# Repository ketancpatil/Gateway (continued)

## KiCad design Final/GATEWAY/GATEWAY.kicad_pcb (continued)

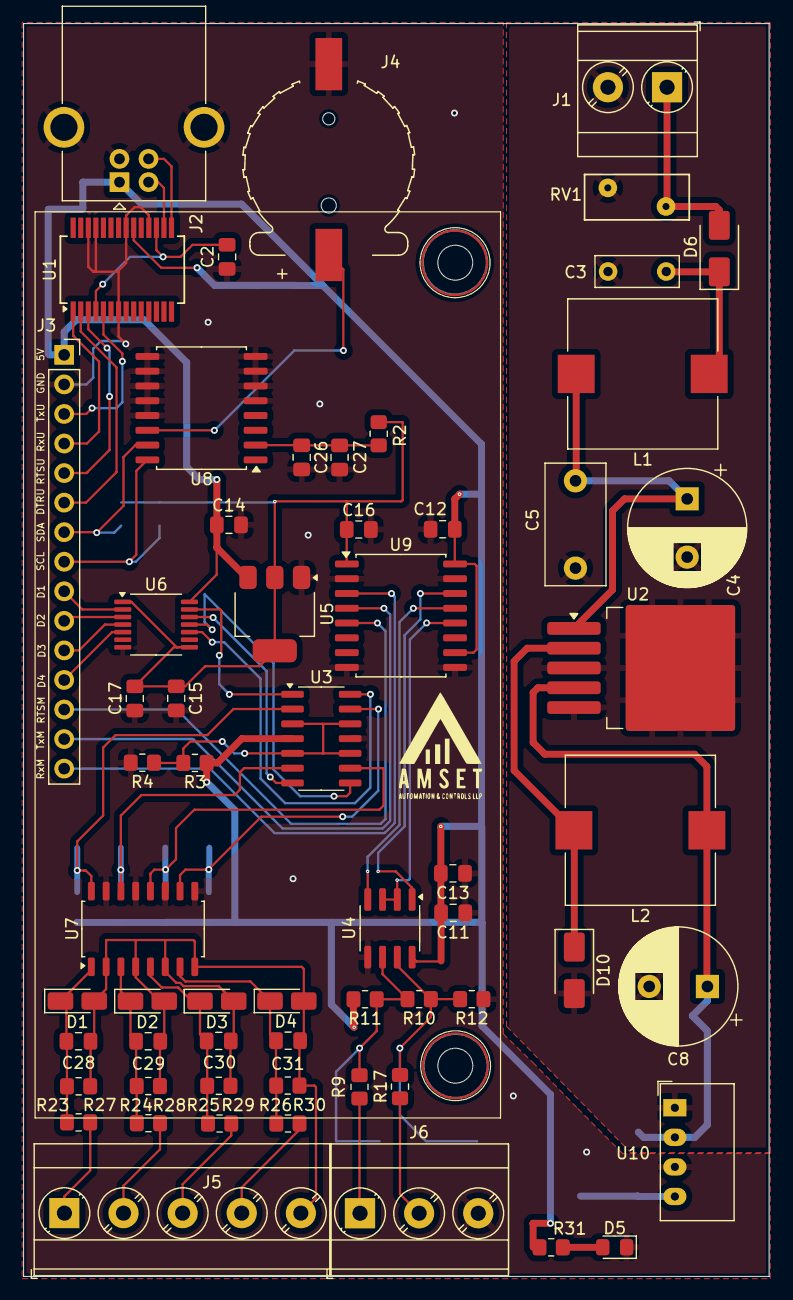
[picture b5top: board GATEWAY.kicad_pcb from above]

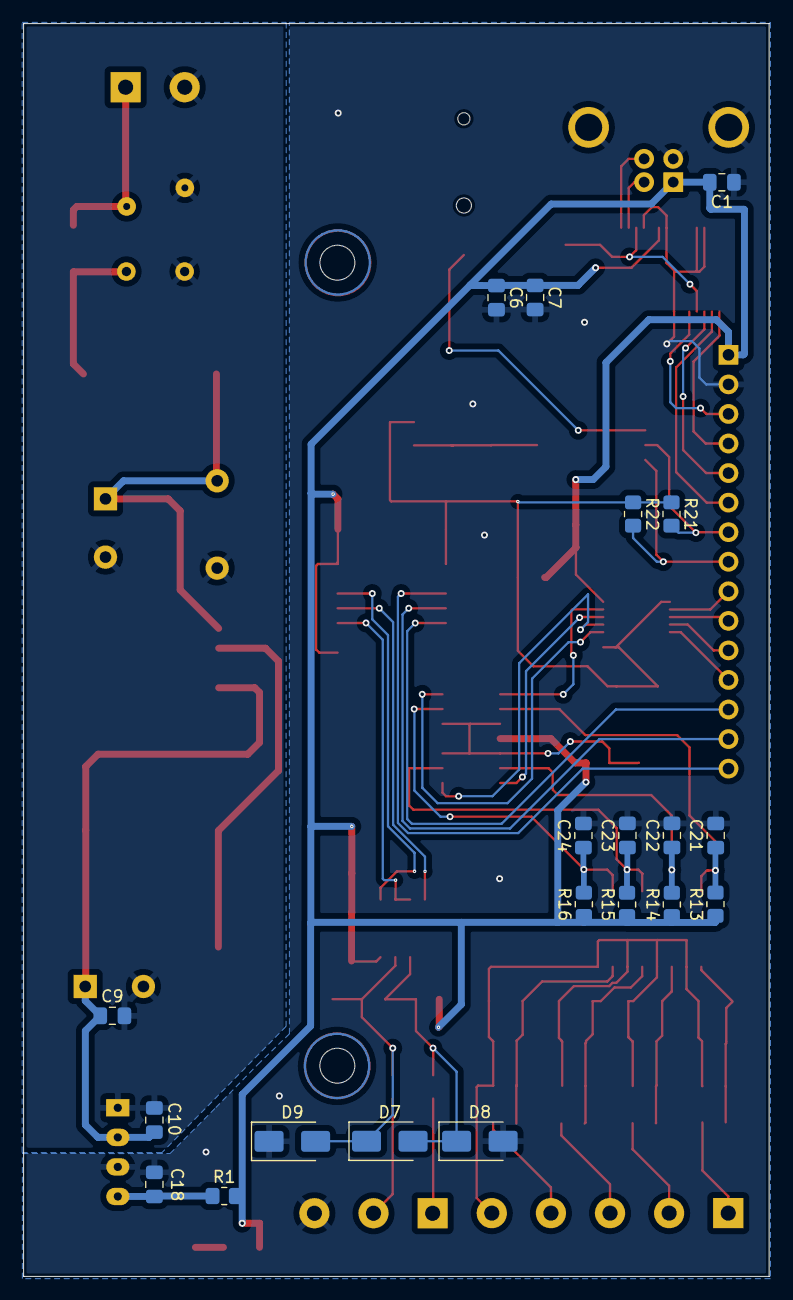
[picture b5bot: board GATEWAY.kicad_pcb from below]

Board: 2 copper layers, 64.1 x 107.7 mm, 81 parts (20 on the bottom side), 54 nets.

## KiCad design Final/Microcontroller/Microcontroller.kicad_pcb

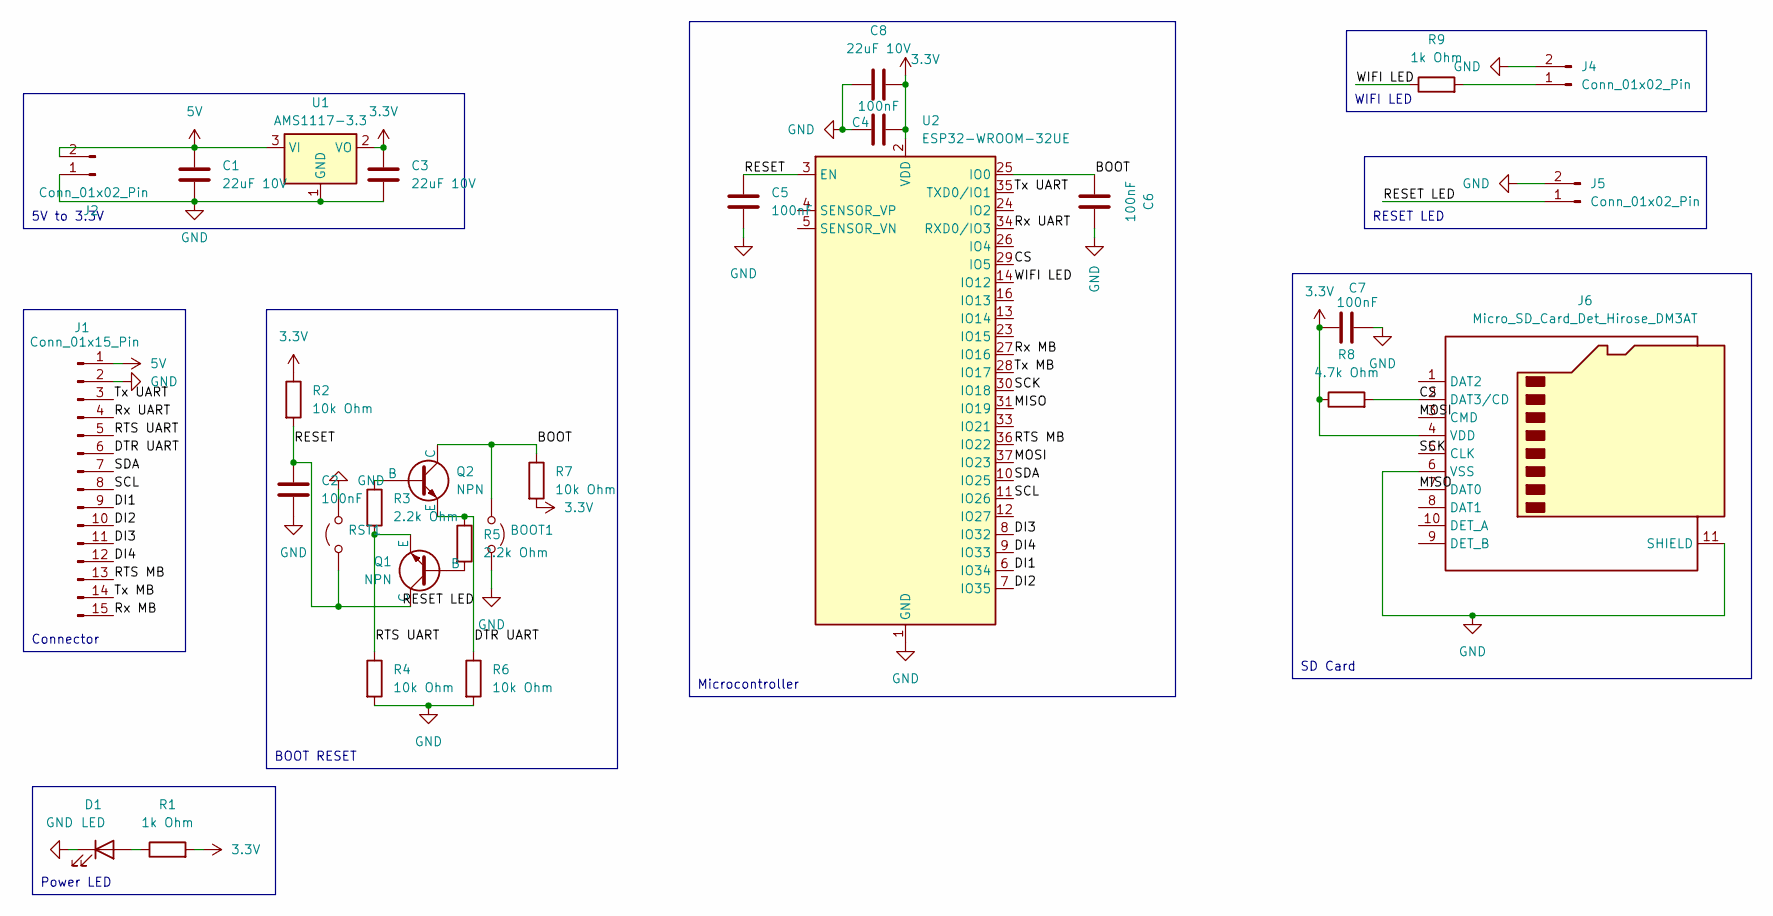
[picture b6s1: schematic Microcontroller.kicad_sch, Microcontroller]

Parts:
BOOT1: SW_SPST_CK_RS282G05A3
C1, C3, C8: 22uF 10V; C_0805_2012Metric_Pad1.18x1.45mm_HandSolder
C2, C4, C5, C6, C7: 100nF; C_0805_2012Metric_Pad1.18x1.45mm_HandSolder
D1: LED; LED_0805_2012Metric_Pad1.15x1.40mm_HandSolder
J1: Conn_01x15_Pin; PinHeader_1x15_P2.54mm_Vertical
J2, J4, J5: Conn_01x02_Pin; JST_XH_B2B-XH-A_1x02_P2.50mm_Vertical
J6: Micro_SD_Card_Det_Hirose_DM3AT; microSD_HC_Hirose_DM3AT-SF-PEJM5
Q1, Q2: NPN; SOT-23_Handsoldering
R1, R9: 1k Ohm; R_0805_2012Metric_Pad1.20x1.40mm_HandSolder
R2, R4, R6, R7: 10k Ohm; R_0805_2012Metric_Pad1.20x1.40mm_HandSolder
R3, R5: 2.2k Ohm; R_0805_2012Metric_Pad1.20x1.40mm_HandSolder
R8: 4.7k Ohm; R_0805_2012Metric_Pad1.20x1.40mm_HandSolder
RST1: JST_XH_B2B-XH-A_1x02_P2.50mm_Vertical
U1: AMS1117-3.3; SOT-223-3_TabPin2
U2: ESP32-WROOM-32UE

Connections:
3.3V: C3.1, C4.1, C7.1, C8.2, J6.4 (VDD), R1.2, R2.1, R7.2, R8.1, U1.2 (VO), U2.2 (VDD)
5V: C1.1, J1.1, J2.2, U1.3 (VI)
/BOOT: BOOT1.1 (A), C6.1, Q2.3 (C), R7.1, U2.25 (IO0)
/CS: J6.2 (DAT3/CD), R8.2, U2.29 (IO5)
/DI1: J1.9, U2.6 (IO34)
/DI2: J1.10, U2.7 (IO35)
/DI3: J1.11, U2.8 (IO32)
/DI4: J1.12, U2.9 (IO33)
/DTR UART: J1.6, Q2.2 (E), R5.1, R6.1
/MISO: J6.7 (DAT0), U2.31 (IO19)
/MOSI: J6.3 (CMD), U2.37 (IO23)
/RESET: C2.1, C5.1, J5.1, Q1.3 (C), R2.2, RST1.1 (A), U2.3 (EN)
/RTS MB: J1.13, U2.36 (IO22)
/RTS UART: J1.5, Q1.2 (E), R3.2, R4.1
/Rx MB: J1.15, U2.27 (IO16)
/Rx UART: J1.4, U2.34 (RXD0/IO3)
/SCK: J6.5 (CLK), U2.30 (IO18)
/SCL: J1.8, U2.11 (IO26)
/SDA: J1.7, U2.10 (IO25)
/Tx MB: J1.14, U2.28 (IO17)
/Tx UART: J1.3, U2.35 (TXD0/IO1)
/WIFI LED: R9.1, U2.14 (IO12)
GND: BOOT1.2 (B), C1.2, C2.2, C3.2, C4.2, C5.2, C6.2, C7.2, C8.1, D1.1 (K), J1.2, J2.1, J4.2, J5.2, J6.6 (VSS), J6.11 (SHIELD), R4.2, R6.2, RST1.2 (B), U1.1 (GND), U2.1 (GND), U2.15 (GND), U2.38 (GND), U2.39 (GND)
unnamed: D1.2 (A), R1.1
unnamed: J4.1, R9.2
unnamed: Q1.1 (B), R5.2
unnamed: Q2.1 (B), R3.1

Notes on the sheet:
Power LED
5V to 3.3V
WIFI LED
SD Card
Microcontroller
Connector
RESET LED
BOOT RESET

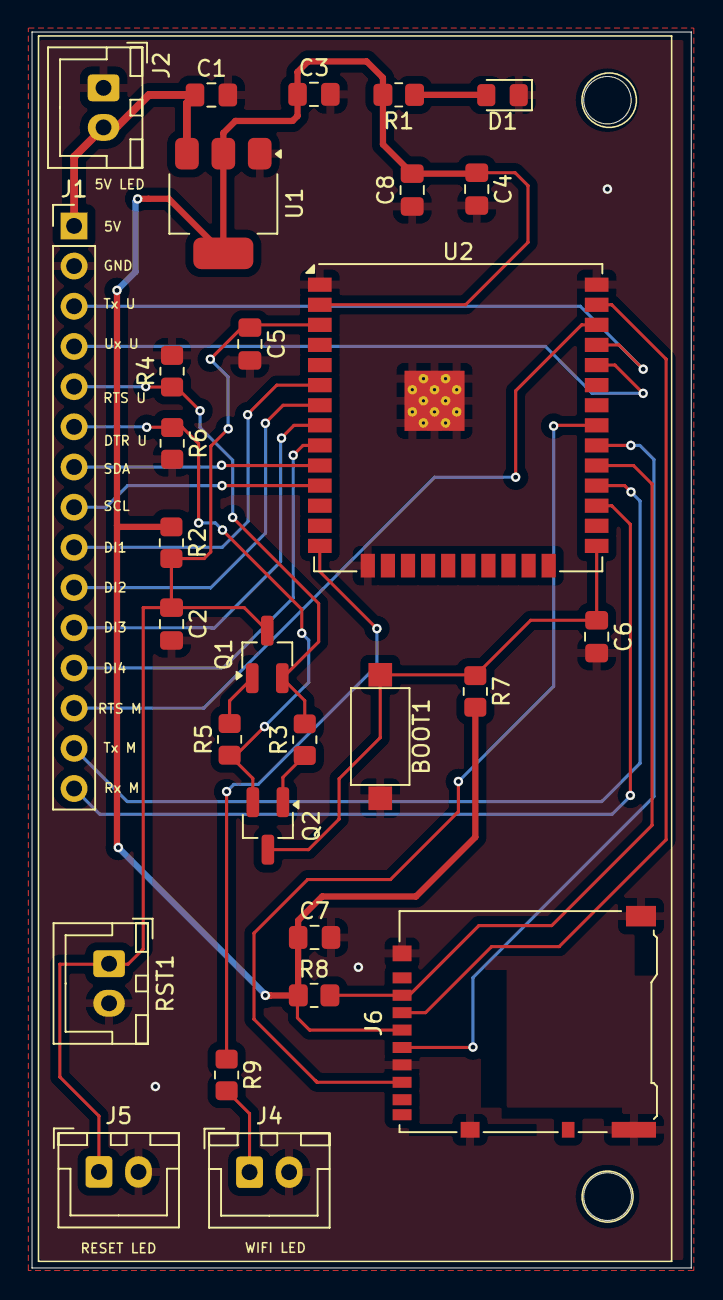
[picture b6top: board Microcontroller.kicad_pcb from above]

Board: 2 copper layers, 41.7 x 78.1 mm, 29 parts (0 on the bottom side), 27 nets.

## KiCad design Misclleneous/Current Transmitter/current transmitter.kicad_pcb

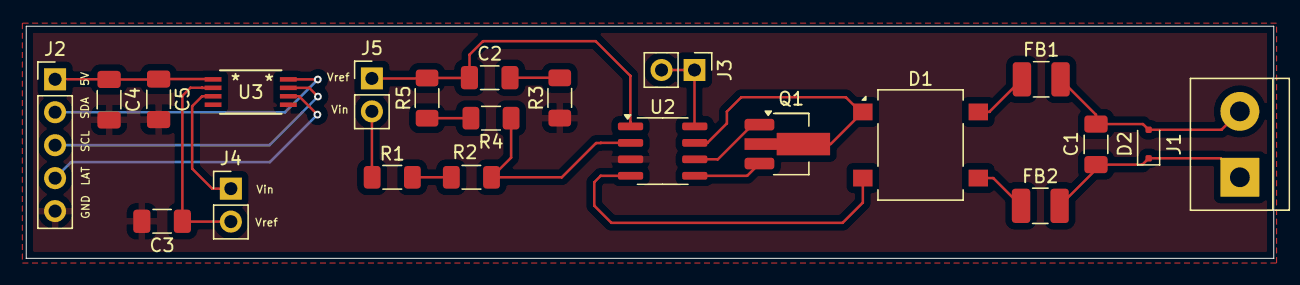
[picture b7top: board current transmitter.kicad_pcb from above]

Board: 2 copper layers, 96.2 x 17.9 mm, 22 parts (0 on the bottom side), 22 nets.

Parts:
C1: 10nF; C_1206_3216Metric_Pad1.33x1.80mm_HandSolder
C2: 2.2uF; C_1206_3216Metric_Pad1.33x1.80mm_HandSolder
C3, C4: 0.1uF; C_1206_3216Metric_Pad1.33x1.80mm_HandSolder
C5: 100pF; C_1206_3216Metric_Pad1.33x1.80mm_HandSolder
D1: ABS4; Diode_Bridge_OnSemi_SDIP-4L
D2: D_TVS; D_SOD-323F
FB1, FB2: FerriteBead; Fuse_1210_3225Metric_Pad1.42x2.65mm_HandSolder
J1: Conn_01x02_Pin; TerminalBlock_bornier-2_P5.08mm
J2: Conn_01x05_Pin; PinHeader_1x05_P2.54mm_Vertical
J3, J4, J5: Conn_01x02_Pin; PinHeader_1x02_P2.54mm_Vertical
Q1: NPN; SOT-89-3_Handsoldering
R1: 100 Ohm; R_1206_3216Metric_Pad1.30x1.75mm_HandSolder
R2: 25.5k Ohm; R_1206_3216Metric_Pad1.30x1.75mm_HandSolder
R3: 50 Ohm; R_1206_3216Metric_Pad1.30x1.75mm_HandSolder
R4: 2.4k Ohm; R_1206_3216Metric_Pad1.30x1.75mm_HandSolder
R5: 100k Ohm; R_1206_3216Metric_Pad1.30x1.75mm_HandSolder
U2: XTR116U; SOIC-8_3.9x4.9mm_P1.27mm
U3: MCP47FEB22A0-E/ST; TSSOP8_ST_MCH

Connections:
/LAT: J2.4, U3.6 (LAT/HVC)
/SCL: J2.3, U3.7 (SCL)
/SDA: J2.2, U3.8 (SDA)
GND: C3.2, C4.2, C5.2, J2.5, R3.1, U2.3 (IRET), U3.5 (VSS)
unnamed: C2.2, R3.2
unnamed: D1.1 (+), Q1.2 (C), U2.7 (V+)
unnamed: D1.2 (-), U2.4 (IO)
unnamed: D1.3, FB2.1
unnamed: D1.4, FB1.1
unnamed: C1.2, D2.1 (A1), FB2.2, J1.1
unnamed: C1.1, D2.2 (A2), FB1.2, J1.2
unnamed: C4.1, C5.1, J2.1, U3.1 (VDD)
unnamed: J3.1, J3.2, U2.8 (VREG)
unnamed: J4.1, U3.3 (VOUT0)
unnamed: C3.1, J4.2, U3.2 (VREF)
unnamed: C2.1, J5.1, R5.2, U2.1 (VREF)
unnamed: J5.2, R1.1
unnamed: Q1.1 (B), U2.6 (B)
unnamed: Q1.3 (E), U2.5 (E)
unnamed: R1.2, R2.1
unnamed: R4.2, R5.1
unnamed: R2.2, R4.1, U2.2 (IIN)

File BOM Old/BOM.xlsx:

Reference | Value | Datasheet | Footprint | Qty | Description | Available | From | Data | Cost per unit | Quantity | Total
C1 | 10nF | ~ | Capacitor_SMD:C_1206_3216Metric_Pad1.33x1.80mm_HandSolder | 1 | Unpolarized capacitor | Yes |  |  |  |  | 0
C2 | 2.2uF | ~ | Capacitor_SMD:C_1206_3216Metric_Pad1.33x1.80mm_HandSolder | 1 | Unpolarized capacitor | Order | Robu | https://robu.in/product/cl31b225kahnnne-samsang-25v-2-2uf-x7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 | 3 | 20 | 60
C3,C4 | 0.1uF | ~ | Capacitor_SMD:C_1206_3216Metric_Pad1.33x1.80mm_HandSolder | 2 | Unpolarized capacitor | Yes |  |  |  |  | 0
C5 | 100pF | ~ | Capacitor_SMD:C_1206_3216Metric_Pad1.33x1.80mm_HandSolder | 1 | Unpolarized capacitor | Order | Robu | https://robu.in/product/1206cg101j500nt-fh-50v-100pf-c0g%c2%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 | 1.4 | 20 | 28
D1 | ABS4 | https://diotec.com/tl_files/diotec/files/pdf/datasheets/abs2.pdf | Diode_SMD:Diode_Bridge_OnSemi_SDIP-4L | 1 | Miniature Glass Passivated Single-Phase Surface Mount Bridge Rectifiers, 280V V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 | Yes |  |  |  |  | 0
D2 | D_TVS | ~ | Diode_SMD:D_SOD-323F | 1 | Bidirectional transient-voltage-suppression diode | Yes |  |  |  |  | 0
FB1,FB2 | FerriteBead | ~ | Fuse:Fuse_1210_3225Metric_Pad1.42x2.65mm_HandSolder | 2 | Ferrite bead | Yes |  |  |  |  | 0
J1 | Conn_01x02_Pin | ~ | TerminalBlock:TerminalBlock_bornier-2_P5.08mm | 1 | Generic connector, single row, 01x02, script generated | Order | Robu |  |  |  | 0
J2 | Conn_01x05_Pin | ~ | Connector_PinHeader_2.54mm:PinHeader_1x05_P2.54mm_Vertical | 1 | Generic connector, single row, 01x05, script generated | Yes |  |  |  |  | 0
J3,J4,J5 | Conn_01x02_Pin | ~ | Connector_PinHeader_2.54mm:PinHeader_1x02_P2.54mm_Vertical | 3 | Generic connector, single row, 01x02, script generated | Yes |  |  |  |  | 0
Q1 | NPN | https://ngspice.sourceforge.io/docs/ngspice-html-manual/manu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 | Package_TO_SOT_SMD:SOT-89-3_Handsoldering | 1 | Bipolar transistor symbol for simulation only, substrate tied to the emitter | Yes |  |  |  |  | 0
R1 | 100 Ohm | ~ | Resistor_SMD:R_1206_3216Metric_Pad1.30x1.75mm_HandSolder | 1 | Resistor | Order | Robu | https://robu.in/product/yageo-100-ohm-1-4w-1206-surface-moun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 | 0.98 | 30 | 29.4
R2 | 25.5k Ohm | ~ | Resistor_SMD:R_1206_3216Metric_Pad1.30x1.75mm_HandSolder | 1 | Resistor | Order | Robu | https://robu.in/product/ac0402fr-0725k5l-yageo-res-thick-fil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 | 0.28999999999999998 | 10 | 2.9
R3 | 50 Ohm | ~ | Resistor_SMD:R_1206_3216Metric_Pad1.30x1.75mm_HandSolder | 1 | Resistor | Order | Robu | https://robu.in/product/ac0402jr-0750rl-yageo-res-thick-film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 | 0.2 | 10 | 2
R4 | 2.4k Ohm | ~ | Resistor_SMD:R_1206_3216Metric_Pad1.30x1.75mm_HandSolder | 1 | Resistor | Order | Robu | https://robu.in/product/rc1206fr-072k4l-yageo-res-thick-film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 | 0.63 | 50 | 31.5
R5 | 100k Ohm | ~ | Resistor_SMD:R_1206_3216Metric_Pad1.30x1.75mm_HandSolder | 1 | Resistor | Yes |  |  |  |  | 0
U2 | XTR116U | http://www.ti.com/lit/ds/symlink/xtr115.pdf | Package_SO:SOIC-8_3.9x4.9mm_P1.27mm | 1 | 4-20mA Current Loop Transmitter, VREF 4.096V, SO-8 | Order | element14 | https://in.element14.com/texas-instruments/xtr116ua-2k5/curr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 | 309.42 | 5 | 1547.1000000000001
U3 | MCP47FEB22A0-E/ST | MCP47FEB22A0-E/ST | MCP47FVBX1:TSSOP8_ST_MCH | 1 |  | Order | element14 | https://in.element14.com/microchip/mcp47feb22a0-e-st/dac-12b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 | 270.22000000000003 | 5 | 1351.1000000000001
 |  |  |  |  |  |  |  |  |  | Total | 3052

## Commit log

2025-08-01 Hello
2025-08-01 Hello1
2025-08-05 sim change
